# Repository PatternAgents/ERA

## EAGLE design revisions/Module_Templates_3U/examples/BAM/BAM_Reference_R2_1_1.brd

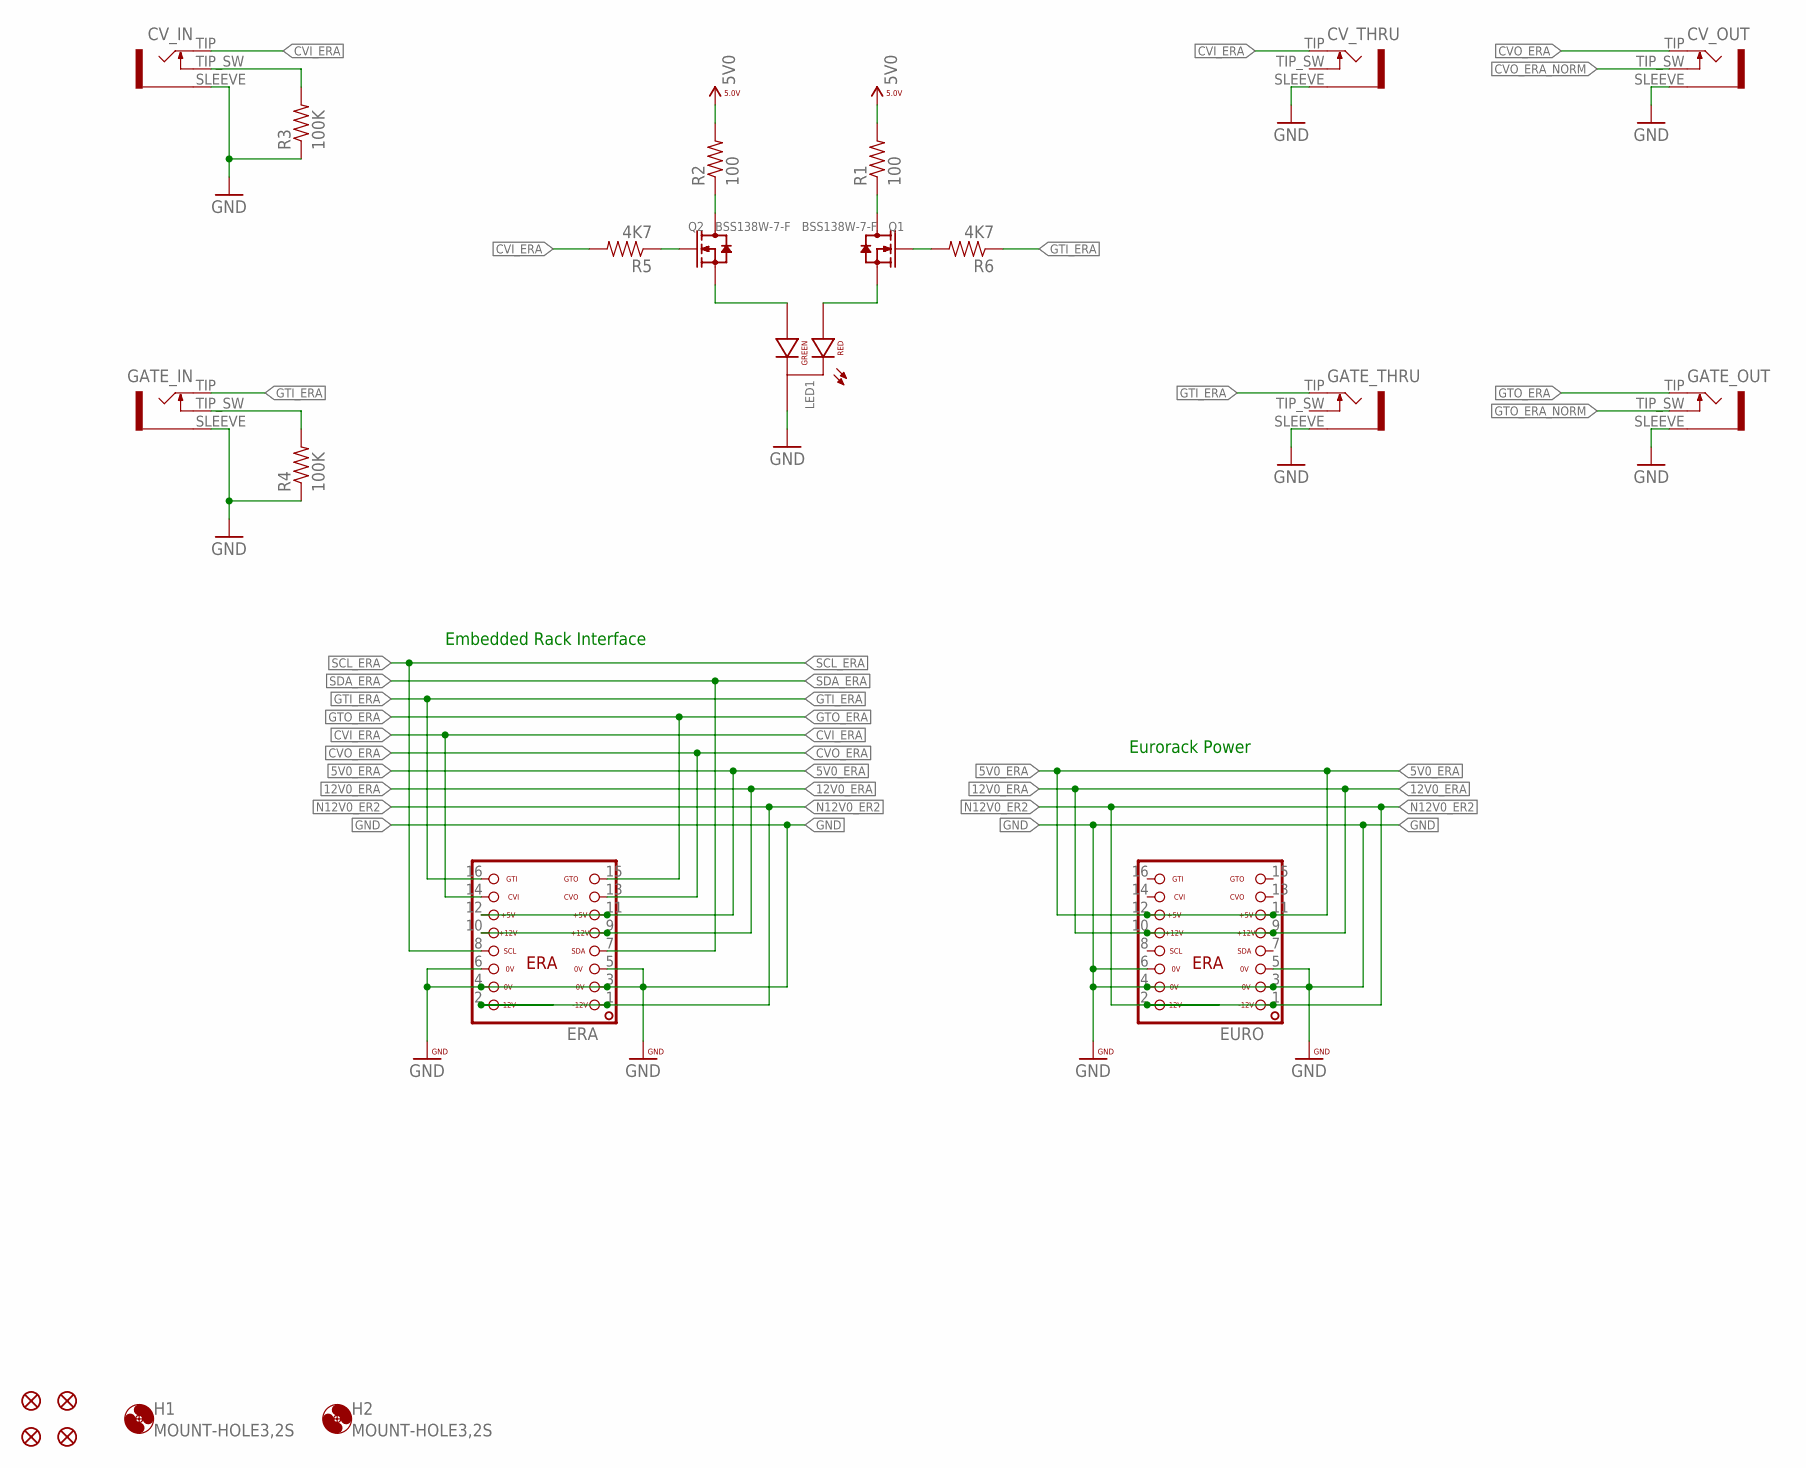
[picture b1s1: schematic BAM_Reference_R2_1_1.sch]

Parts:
CV_IN: JACK-3_5MM-MONO-SW-MJ_3502; MJ-3502
CV_OUT: JACK-3_5MM-MONO-SW-MJ_3502; MJ-3502
CV_THRU: JACK-3_5MM-MONO-SW-MJ_3502; MJ-3502
ERA: ERA-SHROUD; ERA
EURO: ERA-SHROUD; ERA
FID1, FID2, FID3, FID4: FIDUCIALUFIDUCIAL; MICRO-FIDUCIAL
GATE_IN: JACK-3_5MM-MONO-SW-MJ_3502; MJ-3502
GATE_OUT: JACK-3_5MM-MONO-SW-MJ_3502; MJ-3502
GATE_THRU: JACK-3_5MM-MONO-SW-MJ_3502; MJ-3502
H1, H2: MOUNT-HOLE3,2S; 3,2,SMALL
LED1: LED-RG-CC-PTH-G18500; LED-RG-PANEL
Q1, Q2: BSS138W-7-F; SOT-23
R1, R2: 100; 0603-RES
R3, R4: 100K; 0603-RES
R5, R6: 4K7; 0603-RES

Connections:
5V0: R1.2, R2.2
5V0_ERA: ERA.11, ERA.12, EURO.11, EURO.12
12V0_ERA: ERA.9, ERA.10, EURO.9, EURO.10
CVI_ERA: CV_IN.TIP, CV_THRU.TIP, ERA.14, R5.2
CVO_ERA: CV_OUT.TIP, ERA.13
CVO_ERA_NORM: CV_OUT.TIP_SW
GND: CV_IN.SLEEVE, CV_OUT.SLEEVE, CV_THRU.SLEEVE, ERA.3, ERA.4, ERA.5, ERA.6, EURO.3, EURO.4, EURO.5, EURO.6, GATE_IN.SLEEVE, GATE_OUT.SLEEVE, GATE_THRU.SLEEVE, LED1.CC (CATHODE), R3.1, R4.1
GTI_ERA: ERA.16, GATE_IN.TIP, GATE_THRU.TIP, R6.1
GTO_ERA: ERA.15, GATE_OUT.TIP
GTO_ERA_NORM: GATE_OUT.TIP_SW
N12V0_ER2: ERA.1, ERA.2, EURO.1, EURO.2
unnamed: LED1.GREEN (GREEN_CATHODE), Q2.2 (S)
unnamed: LED1.RED (RED_CATHODE), Q1.2 (S)
unnamed: Q2.3 (D), R2.1
unnamed: Q1.3 (D), R1.1
unnamed: Q2.1 (G), R5.1
unnamed: Q1.1 (G), R6.2
unnamed: CV_IN.TIP_SW, R3.2
unnamed: GATE_IN.TIP_SW, R4.2
SCL_ERA: ERA.8
SDA_ERA: ERA.7

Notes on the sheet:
Embedded Rack Interface
Eurorack Power

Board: 2 copper layers, 23 parts (0 on the bottom side), 17 nets, no tracks yet.

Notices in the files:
parts and their libraries:
PatternAgents-Beautify: License : http://creativecommons.org/licenses/by-sa/3.0
(Creative Commons 3.0)
